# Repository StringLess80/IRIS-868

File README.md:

<div align="center">

# 📡 IRIS-868

**Custom embedded RF platform for the 868 MHz ISM band**

IRIS-868 is a custom embedded RF platform based on the STM32F303RET6 microcontroller and an Ebyte E22-900M22S (Semtech SX1262) sub-GHz LoRa module, designed for 868 MHz ISM-band wireless communication and data logging.

<br/>

<br/>

</div>

---

## ⚡ At a glance

|  |  |
|---|---|
| 🧠 **MCU** | STM32F303RET6 · Cortex-M4F @ 72 MHz · 512 KB flash · 64 + 16 KB RAM |
| 📻 **Radio** | Ebyte E22-900M22S · SX1262 · +22 dBm · LoRa / (G)FSK |
| 💾 **Storage** | Winbond W25Q128JV · 128 Mbit (16 MiB) SPI NOR flash for data logging |
| 🔌 **Power** | USB micro-B → AP2112K-3.3 LDO, filtered analog and RF rails, VBUS voltage monitoring on the ADC |
| 🧩 **Expansion** | 2 × 12-pin edge headers · I²C header for 128×64 OLED · 5-pin SWD with NRST · BOOT0 jumper · user button |
| 📐 **Board** | 2-layer FR4 · 78.8 × 36.6 mm · green mask, white silk · components on both sides |
| 🛠️ **Tooling** | KiCad 10, footprints and symbols embedded in the project files |

> [!WARNING]
> **Revision B is design-complete but has not been bring-up tested.** Fabrication files are released as-is. No firmware is included in this repository yet.

## 📑 Table of contents

- [What's new in revision B](#-whats-new-in-revision-b)
- [Gallery](#%EF%B8%8F-gallery)
- [System architecture](#%EF%B8%8F-system-architecture)
- [Repository layout](#-repository-layout)
- [Hardware overview](#-hardware-overview)
- [Pin assignment](#-pin-assignment)
- [Board specification](#-board-specification)
- [Bill of materials](#-bill-of-materials)
- [Getting started](#-getting-started)
- [Releases](#-releases)

## 🆕 What's new in revision B

| Area | Revision A | Revision B |
|---|---|---|
| **Expansion** | Most GPIOs unrouted | Two 1×12 edge headers (J5, J7) bring out power, reset, BOOT0, USART1 and 13 GPIOs |
| **Debug** | 4-pin SWD, no NRST | 5-pin SWD **with NRST** — "connect under reset" now works |
| **Storage** | — | 16 MiB W25Q128JV SPI flash on SPI3 (bottom side) |
| **User input** | Reset button only | Additional user button on **PC13** with RC debounce |
| **Monitoring** | — | VBUS divider (47 kΩ / 15 kΩ) on **PC0** for USB voltage measurement |
| **USB** | D+ pull-up fixed to +3.3 V | D+ pull-up driven by **PB8** — firmware-controlled attach/detach |
| **Radio** | E220-900M22S (LLCC68) | E22-900M22S (SX1262), same MCU connections |
| **Boot** | BOOT0 floats with no jumper | 100 kΩ pull-down (R13), boots from flash with no jumper |
| **Board** | 74.2 × 32.0 mm, single-sided assembly | 78.8 × 36.6 mm, bottom-side SMD parts and headers |

A design review before release added these changes:

- **RF feed:** the antenna trace no longer runs under the module, and J6 moved to suit (see [RF chain](#rf-chain)).
- **Decoupling:** C10 now sits next to the NRST pin, and C8 next to the VDDA pin.
- **Clean-up:** the unused test pad under IC1 was removed.
- **Fabrication:** design constraints follow JLCPCB's limits, with a green mask so the solder dams between LQFP pins can be kept.

## 🖼️ Gallery

<div align="center">

| Front | Back |
|:---:|:---:|
|  |  |

</div>

📄 Full schematic: [`docs/schematics/IRIS-868.pdf`](docs/schematics/IRIS-868.pdf)

## 🏗️ System architecture

```mermaid
flowchart LR
    USB["USB micro-B<br/>J2"] -->|VBUS 5 V| LDO["AP2112K-3.3<br/>600 mA LDO"]
    USB -.->|"D+ / D-"| ESD["USBLC6-2SC6<br/>ESD"]
    ESD -.-> MCU
    USB -->|"VBUS ÷ 4.13"| VMON["V_MON<br/>PC0 / ADC"]
    VMON --> MCU

    LDO --> RAIL(("3.3 V"))
    RAIL -->|"FB1 120 Ω"| VDDA["+3.3VA"]
    RAIL -->|"FB2 120 Ω"| VRF["VRF"]
    RAIL --> MCU
    VDDA --> MCU
    VRF --> MOD

    MCU["STM32F303RET6<br/>Cortex-M4F @ 72 MHz"]
    MCU <-->|"SPI1 · NSS · BUSY · DIO1 · NRST"| MOD["E22-900M22S<br/>SX1262 · +22 dBm"]
    MCU -->|"RXEN / TXEN"| MOD
    MOD -->|ANT| SMA["SMA edge<br/>J6"]

    MCU <-->|"SPI3 · CS"| FLASH["W25Q128JV<br/>16 MiB flash"]
    MCU <-->|"I²C1"| OLED["128×64 OLED<br/>header"]
    MCU <-->|"SWD + NRST"| DBG["ST-Link<br/>J3"]
    MCU <-->|"GPIO · USART1"| HDR["Edge headers<br/>J5 / J7"]
    BTN["User button<br/>PC13"] --> MCU
    MCU -.->|BOOT0| JMP["Boot jumper"]

    style MCU fill:#03234B,color:#fff
    style MOD fill:#2ea44f,color:#fff
    style FLASH fill:#8e44ad,color:#fff
    style RAIL fill:#f39c12,color:#fff
```

## 📁 Repository layout

```
IRIS-868/
├── CHANGELOG.md               Release history
├── hardware/
│   ├── kicad/                 KiCad 10 project (schematic, PCB, design rules)
│   │   └── libs/              Source symbols, footprints, 3D models
│   └── gerbers/
│       ├── rev.A/             Gerber and Excellon files, revision A
│       └── rev.B/             Gerber and Excellon files, revision B
├── production/BOM/            Interactive BOM for assembly
└── docs/
    ├── schematics/            Schematic PDF
    ├── images/                Board renders by revision
    └── datasheets/            Component reference documents
```

The schematic uses four top-level sheets, a KiCad 10 feature: MCU, crystal, reset, VBUS monitor and edge headers (`IRIS-868.kicad_sch`), power and USB (`pwr.kicad_sch`), the radio (`rf.kicad_sch`), and connectors, flash and the user button (`interfaces.kicad_sch`).

## 🔧 Hardware overview

### Power

USB VBUS feeds an **AP2112K-3.3** LDO (SOT-23-5, 600 mA) that generates the single 3.3 V system rail. Three domains branch from it:

| Rail | Source | Decoupling | Purpose |
|---|---|---|---|
| `+3.3V` | LDO output | 10 µF + 7 × 100 nF + 2 × 1 µF | MCU digital, I/O, flash, headers |
| `+3.3VA` | via FB1 (120 Ω ferrite) | 1 µF + 10 nF | STM32 VDDA / analog reference |
| `VRF` | via FB2 (120 Ω ferrite) | 22 µF + 1 µF + 2 × 100 nF | RF module supply |

The ferrite beads isolate the analog and RF domains from digital switching noise on the main rail, and C7 and C8 sit next to the VDDA pin. The 22 µF bulk capacitor on `VRF` supplies the current burst drawn by the module during transmission.

VBUS and +3.3 V are both available on header J5, so the board can supply a small carrier or add-on board.

### VBUS monitoring

A 47 kΩ / 15 kΩ divider (R6 / R7) scales VBUS onto `V_MON` (**PC0**, ADC12_IN6), filtered by C20 (100 nF). The divider ratio is 15 / 62, so 5.0 V on VBUS reads as about 1.21 V, and firmware recovers VBUS as `V_MON × 4.133`. The divider draws roughly 80 µA from VBUS, and its ~11 kΩ source impedance combined with C20 gives a stable input for the ADC sample-and-hold.

### RF chain

The E22-900M22S connects to the MCU over SPI1 plus four control lines. `RXEN` and `TXEN` drive the module's internal RF switch and must be managed by firmware around every transmit/receive transition. The antenna net (`ANT`) leaves the module's stamp-hole RF pad away from the module body and reaches the SMA edge connector as a 7.4 mm, 1.0 mm-wide coplanar trace on F.Cu, over an unbroken ground plane on B.Cu. A project design rule sets a 0.15 mm gap to the surrounding copper, which gives a calculated impedance of about 50 Ω with a 1.51 mm dielectric and εr 4.5. GND vias flank the feed.

### Data-logging flash

A **Winbond W25Q128JVSIQ** (SOIC-8, 208 mil) on the bottom side provides 16 MiB of non-volatile storage on **SPI3** (PC10 / PC11 / PC12) with chip select on **PD2**. The CS line has a 10 kΩ pull-up (R8) so the flash stays deselected while the MCU is in reset. `/WP` and `/HOLD` are tied high through R9 and R10, so the device operates in standard single-bit SPI mode; dual/quad I/O is not available on this revision. C21 decouples the flash locally.

### User input and reset

| Button | Net | Circuit |
|---|---|---|
| **SW1** (RST) | NRST (pin 7) | Pulls NRST low. 100 nF (C10) sits next to the pin on the bottom side. NRST is also on the SWD header and J5 |
| **SW2** (PC13) | PC13 (pin 2) | Active-low. 10 kΩ pull-up (R11), 10 kΩ series (R12), 100 nF (C22) to GND — about 1 ms fall / 2 ms rise debounce |

### USB

The USB D+ 1.5 kΩ pull-up (R2) is connected to **PB8** rather than to +3.3 V. Firmware must drive PB8 high to signal device attach to the host, and can drive it low to force a clean disconnect/re-enumeration without unplugging the cable.

### Interfaces

| Connector | Type | Pinout |
|---|---|---|
| **J2** USB | micro-B | USB FS device on PA11/PA12, D+ pull-up switched by PB8, ESD-protected |
| **J3** SWD | 1×5 @ 2.54 mm | `GND` · `NRST` · `SWCLK` · `SWDIO` · `+3.3V` |
| **J1** (BOOT0) | 1×3 @ 2.54 mm | `GND` · `BOOT0` · `+3.3V` — no jumper or 1–2 = flash, 2–3 = bootloader |
| **J4** (OLED) | 1×4 @ 2.54 mm | `GND` · `+3.3V` · `SCL` · `SDA` (1.5 kΩ pull-ups on board) |
| **J5** | 1×12 @ 2.54 mm, bottom-mounted | Power, reset, BOOT0, USART1, GPIO — see below |
| **J7** | 1×12 @ 2.54 mm, bottom-mounted | GPIO — see below |
| **J6** SMA | edge-mount | Antenna |

### Edge headers

J5 and J7 run along the long edges of the board with a row-to-row spacing of 31.75 mm (1.25 in). The header bodies are mounted on the bottom side, so the board can be plugged into a carrier with the components facing up. Pin 1 of each header is at the USB end.

| Pin | **J5** | **J7** |
|:---:|---|---|
| 1 | `GND` | `PB9` |
| 2 | `+3.3V` | `GND` |
| 3 | `VBUS` (5 V) | `PB0` |
| 4 | `NRST` | `PB1` |
| 5 | `BOOT0` | `PC4` |
| 6 | `PA9` (USART1_TX) | `PC5` |
| 7 | `PA10` (USART1_RX) | `PC6` |
| 8 | `GND` | `PC7` |
| 9 | `PB4` | `PC8` |
| 10 | `PB5` | `GND` |
| 11 | `PB6` | not connected |
| 12 | `PB8` ⚠️ USB D+ pull-up | not connected |

## 📌 Pin assignment

### STM32F303RET6 ↔ E22-900M22S

| STM32 pin | Signal | Module pin | Direction | Function |
|---|---|---|:---:|---|
| `PA5` | SPI1_SCK | 18 (SCK) | → | SPI clock |
| `PA6` | SPI1_MISO | 16 (MISO) | ← | SPI data out |
| `PA7` | SPI1_MOSI | 17 (MOSI) | → | SPI data in |
| `PA4` | NSS | 19 (NSS) | → | Chip select, active low |
| `PA3` | NRST | 15 (NRST) | → | Module reset, active low |
| `PA2` | BUSY | 14 (BUSY) | ← | Transceiver busy status |
| `PA8` | DIO1 | 13 (DIO1) | ← | Primary interrupt line |
| `PB10` | RXEN | 6 (RXEN) | → | RF switch, receive enable |
| `PB11` | TXEN | 7 (TXEN) | → | RF switch, transmit enable |

Module pin 8 (DIO2) is left unconnected in revision B.

### STM32F303RET6 ↔ W25Q128JV

| STM32 pin | Signal | Flash pin | Direction |
|---|---|---|:---:|
| `PC10` | SPI3_SCK | 6 (CLK) | → |
| `PC11` | SPI3_MISO | 2 (DO) | ← |
| `PC12` | SPI3_MOSI | 5 (DI) | → |
| `PD2` | FLASH_CS | 1 (/CS) | → |

<details>
<summary><b>Other pin assignments</b></summary>

<br/>

| STM32 pin | Function |
|---|---|
| `PA11` / `PA12` | USB D− / D+ |
| `PB8` | USB D+ pull-up control (also on J5 pin 12) |
| `PA13` / `PA14` | SWDIO / SWCLK |
| `PA15` | I²C1 SCL (AF4) |
| `PB7` | I²C1 SDA (AF4) |
| `PC0` | V_MON — VBUS voltage divider (ADC) |
| `PC13` | User button, active low |
| `PF0` / `PF1` | 16 MHz crystal (OSC_IN / OSC_OUT) |
| `NRST` (pin 7) | Reset button + 100 nF, SWD header, J5 |
| `BOOT0` (pin 60) | J1 via 10 kΩ (R1), 100 kΩ pull-down (R13), J5 (direct) |
| `PA9`, `PA10`, `PB4`–`PB6` | J5 |
| `PB0`, `PB1`, `PB9`, `PC4`–`PC8` | J7 |

The remaining GPIOs — `PA0`, `PA1`, `PB2`, `PB3`, `PB12`–`PB15`, `PC1`–`PC3`, `PC9`, `PC14`, `PC15` — are **not routed** in revision B.

</details>

## 📐 Board specification

| Parameter | Value |
|---|---|
| Dimensions | 78.8 × 36.6 mm, 2 mm corner radius |
| Layers | 2 (F.Cu / B.Cu), GND pour on both |
| Stackup | 1.6 mm FR4, 35 µm copper, εr 4.5 |
| Finish | HASL, green solder mask, white silkscreen |
| Vias | 327, 0.6 mm with 0.3 mm drill, tented |
| Minimum rules | Track 0.15 mm, clearance 0.2 mm, annular ring 0.13 mm, hole-to-hole 0.5 mm, copper-to-edge 0.2 mm |
| Assembly | Double-sided (U4, R8–R10, R13, C10, C21 and header bodies on the bottom) |
| Special rules | 0.15 mm clearance on the `ANT` coplanar feedline |

## 🧾 Bill of materials

<details>
<summary><b>Full BOM — 53 components</b></summary>

<br/>

| Ref | Qty | Value | Package | Notes |
|---|:---:|---|---|---|
| U1 | 1 | STM32F303RET6 | LQFP-64 | 0.5 mm pitch |
| U2 | 1 | AP2112K-3.3 | SOT-23-5 | 600 mA LDO |
| U3 | 1 | USBLC6-2SC6 | SOT-23-6 | USB ESD protection |
| U4 | 1 | W25Q128JVSIQ | SOIC-8 5.3 × 5.3 mm | 128 Mbit SPI flash, **bottom side** |
| IC1 | 1 | E22-900M22S | Ebyte SMD module | SX1262, +22 dBm |
| Y1 | 1 | 16 MHz | 3225-4pin | CL ≈ 10 pF, ≤20 ppm recommended |
| C1–C5, C10, C16, C17, C19, C21 | 10 | 100 nF | 0402 | 16 V X7R — C10 and C21 on bottom side |
| C20, C22 | 2 | 100 nF | 0805 | 16 V X7R — V_MON filter, PC13 debounce |
| C8, C9, C14, C15 | 4 | 1 µF | 0402 | 16 V X5R/X7R |
| C13 | 1 | 1 µF | 0402 | **25 V** — sits on the 5 V VBUS rail |
| C6 | 1 | 10 µF | 0603 | 16 V X5R |
| C18 | 1 | 22 µF | 0805 | 16 V X5R, RF bulk |
| C7 | 1 | 10 nF | 0402 | 16 V X7R, VDDA filter |
| C11, C12 | 2 | 12 pF | 0402 | **50 V C0G/NP0 ±5%**, crystal load |
| R1 | 1 | 10 kΩ | 0402 | BOOT0 series |
| R2 | 1 | 1.5 kΩ | 0402 | USB D+ pull-up (to PB8) |
| R3 | 1 | 1.5 kΩ | 0402 | Power LED series |
| R4, R5 | 2 | 1.5 kΩ | 0402 | I²C pull-ups |
| R6 | 1 | 47 kΩ | 0402 | VBUS divider, top — 1% recommended |
| R7 | 1 | 15 kΩ | 0402 | VBUS divider, bottom — 1% recommended |
| R8, R9, R10 | 3 | 10 kΩ | 0402 | Flash /CS, /WP, /HOLD pull-ups, **bottom side** |
| R11, R12 | 2 | 10 kΩ | 0402 | PC13 button pull-up / series |
| R13 | 1 | 100 kΩ | 0402 | BOOT0 pull-down, **bottom side** |
| FB1, FB2 | 2 | 120 Ω @ 100 MHz | 0402 | Analog / RF rail filtering, rated ≥ 500 mA |
| D1 | 1 | Red LED | 0603 | Power indicator |
| SW1, SW2 | 2 | Tactile switch | 6 mm THT | 4-pin, 4.5 × 6.5 mm, marked RST and PC13 |
| J1 | 1 | Pin header 1×3 | 2.54 mm | BOOT0 select, marked BOOT0 |
| J2 | 1 | USB micro-B | Würth 629105150521 | |
| J3 | 1 | Pin header 1×5 | 2.54 mm | SWD + NRST |
| J4 | 1 | Pin header 1×4 | 2.54 mm | I²C / OLED, marked OLED |
| J5, J7 | 2 | Pin header 1×12 | 2.54 mm | Edge headers, **bottom side** |
| J6 | 1 | SMA edge-mount | RF Solutions CON-SMA-EDGE-S | |

</details>

For assembly, open the [interactive BOM](production/BOM/IRIS-868_iBOM_revB.html) after downloading it.

> [!TIP]
> Capacitor voltage ratings account for MLCC **DC bias derating** — class II ceramics lose a large fraction of their nominal capacitance near their rated voltage, so ratings are specified at roughly 4–5× the working voltage. A **2.54 mm jumper shunt** on J1 is needed only to enter the bootloader, and it isn't part of the PCB BOM.

## 🚀 Getting started

<details open>
<summary><b>1 · Fabricate the board</b></summary>

<br/>

Fabrication files for revision B are in [`hardware/gerbers/rev.B/`](hardware/gerbers/rev.B/), as Gerber and Excellon drill files. A ready-to-upload zip is attached to the [`v2.0.0` release](https://github.com/StringLess80/IRIS-868/releases/tag/v2.0.0).

- Process: standard 2-layer, 1.6 mm FR4, 1 oz copper, HASL or ENIG, green mask
- No controlled impedance is specified
- Revision B has SMD parts on **both sides**. If using assembly service, request double-sided assembly or have the bottom-side parts (U4, R8–R10, R13, C10, C21) left unpopulated and fit them by hand
- Suggested hand-assembly order: bottom-side SMD parts first, then the STM32 (drag solder, then inspect with flux and a loupe), then the remaining ICs, then passives, then the module, then through-hole parts last — edge headers J5/J7 go in from the bottom

</details>

<details>
<summary><b>2 · Open the design</b></summary>

<br/>

The project requires **KiCad 10** or later, because it uses multiple top-level sheets. Symbols and footprints are embedded in the project files, so it opens without any library setup. Sources for the non-standard parts (E22 module, SMA edge connector) and the 3D models are under `hardware/kicad/libs/`. DRC reports one library warning on J6, because its source library is not registered in the project.

```bash
git clone https://github.com/StringLess80/IRIS-868.git
cd IRIS-868
kicad hardware/kicad/IRIS-868.kicad_pro
```

</details>

<details>
<summary><b>3 · Program it</b></summary>

<br/>

**Via SWD (recommended)** — connect an ST-Link or any CMSIS-DAP probe to J3, including the NRST line. Because NRST is on the header, "connect under reset" works, so a board with firmware that disables SWD or enters low-power mode early can still be recovered from the debugger.

```bash
st-flash --reset write firmware.bin 0x08000000
```

**Via UART bootloader** — connect a 3.3 V USB-serial adapter to J5 (`PA9` = MCU TX, `PA10` = MCU RX, `GND`), fit the J1 jumper on pins 2–3 and reset:

```bash
stm32flash -w firmware.bin -v -g 0x0 /dev/ttyUSB0
```

**Via USB DFU** — the ROM bootloader does not drive PB8, so the D+ pull-up is inactive and the host will not see the device. Tie J5 pin 12 (`PB8`) to J5 pin 2 (`+3.3V`) for the duration of the DFU session, fit the J1 jumper on pins 2–3, reset, then:

```bash
dfu-util -a 0 -s 0x08000000:leave -D firmware.bin
```

> [!CAUTION]
> Remove the PB8 link before running application firmware — if firmware drives PB8 low while it is tied to +3.3 V, the pin is shorted.

Remove the jumper, or move it to pins 1–2, and reset to run from flash.

</details>

## 📦 Releases

| Version | Hardware | Status |
|---|---|---|
| [`v2.0.0`](https://github.com/StringLess80/IRIS-868/releases/tag/v2.0.0) | Revision B | Released for fabrication, not bring-up tested |
| [`v1.0.0`](https://github.com/StringLess80/IRIS-868/releases/tag/v1.0.0) | Revision A | Superseded |

The major version changes with each PCB revision. Minor and patch versions cover compatible changes to the BOM, documentation or fabrication outputs. See the [changelog](CHANGELOG.md) for details.

<div align="center">
<br/>

Made with [KiCad](https://www.kicad.org/) 🛠️

</div>

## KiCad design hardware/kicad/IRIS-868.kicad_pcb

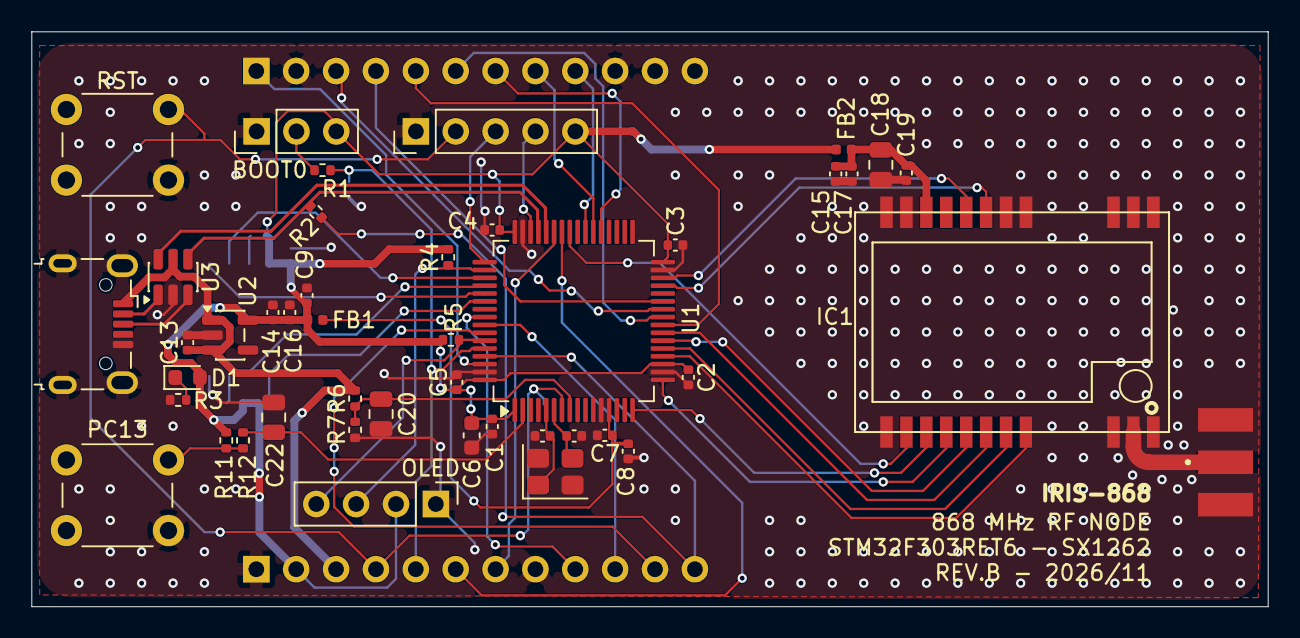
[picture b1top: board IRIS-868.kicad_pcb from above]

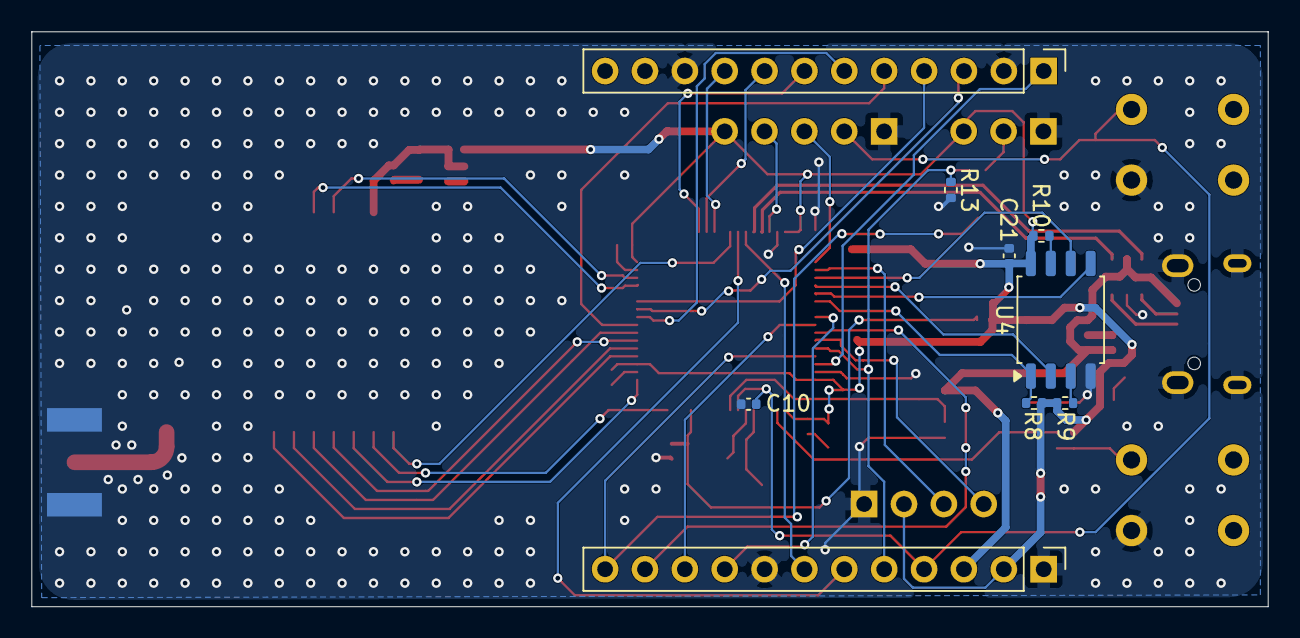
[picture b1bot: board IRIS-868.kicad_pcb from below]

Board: 2 copper layers, 78.8 x 36.6 mm, 53 parts (9 on the bottom side), 52 nets.

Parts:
C1, C2, C3, C4, C5, C10, C16, C17, C19, C21: 100 nF; C_0402_1005Metric
C6: 10 uF; C_0603_1608Metric
C7: 10 nF; C_0402_1005Metric
C8, C9, C13, C14, C15: 1 uF; C_0402_1005Metric
C11, C12: 12 pF; C_0402_1005Metric
C18: 22 uF; C_0805_2012Metric
C20, C22: 100 nF; C_0805_2012Metric
D1: RED; LED_0603_1608Metric
FB1, FB2: 120 R; L_0402_1005Metric
IC1: E22-900M22S
J1: PRG; PinHeader_1x03_P2.54mm_Vertical
J2: USB_B_Micro; USB_Micro-B_Wuerth_629105150521
J3: SWD; PinHeader_1x05_P2.54mm_Vertical
J4: 128x64 OLED; PinHeader_1x04_P2.54mm_Vertical
J5, J7: Conn_01x12_Pin; PinHeader_1x12_P2.54mm_Vertical
J6: SMA; RFSOLUTIONS_CON-SMA-EDGE-S
R1: 10 k; R_0402_1005Metric
R2, R3, R4, R5: 1k5; R_0402_1005Metric
R6: 47k; R_0402_1005Metric
R7: 15k; R_0402_1005Metric
R8, R9, R10, R11, R12: 10k; R_0402_1005Metric
R13: 100k; R_0402_1005Metric
SW1: RST; SW_PUSH_6mm
SW2: BTN; SW_PUSH_6mm
U1: STM32F303RET6; LQFP-64_10x10mm_P0.5mm
U2: AP2112K-3.3; SOT-23-5
U3: USBLC6-2SC6; SOT-23-6
U4: W25Q128JVSIQ; SOIC-8_5.3x5.3mm_P1.27mm
Y1: 16 MHz; Crystal_SMD_3225-4Pin_3.2x2.5mm

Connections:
+3.3V: C1.1, C2.1, C3.1, C4.1, C5.1, C6.1, C9.1, C14.1, C16.1, C21.1, D1.2 (A), FB1.2, FB2.1, J1.3, J3.5, J4.2, J5.2, R4.2, R5.2, R8.1, R9.1, R10.1, R11.2, U1.1 (VBAT), U1.19 (VDD), U1.32 (VDD), U1.48 (VDD), U1.64 (VDD), U2.5 (VOUT), U4.8 (VCC)
+3.3VA: C7.1, C8.1, FB1.1, U1.13 (VDDA)
/PWR-USB/PWR_LED_K: D1.1 (K), R3.2
/Root/J_BOOT0: J1.2, R1.1
ANT: IC1.21 (ANT), J6.1
BOOT0: J5.5, R1.2, R13.1, U1.60 (BOOT0)
BTN: C22.1, R12.1, U1.2 (PC13)
BUSY: IC1.14 (BUSY), U1.16 (PA2)
DIO1: IC1.13 (DIO1), U1.41 (PA8)
FLASH_~CS: R8.2, U1.54 (PD2), U4.1 (~CS)
GND: C1.2, C2.2, C3.2, C4.2, C5.2, C6.2, C7.2, C8.2, C9.2, C10.2, C11.2, C12.2, C13.2, C14.2, C15.2, C16.2, C17.2, C18.2, C19.2, C20.2, C21.2, C22.2, IC1.1 (GND), IC1.2 (GND), IC1.3 (GND), IC1.4 (GND), IC1.5 (GND), IC1.10 (GND), IC1.11 (GND), IC1.12 (GND), IC1.20 (GND), IC1.22 (GND), J1.1, J2.5 (GND), J2.SH (Shield), J3.1, J4.1, J5.1, J5.8, J6.G1, J6.G2, J6.G3, J6.G4, J7.2, J7.10, R3.1, R7.1, R13.2, SW1.2, SW2.2, U1.12 (VSSA), U1.18 (VSS), U1.31 (VSS), U1.47 (VSS), U1.63 (VSS), U2.2 (GND), U3.2 (GND), U4.4 (GND), Y1.2 (G), Y1.4 (G)
I2C1_SCL: J4.3, R4.1, U1.50 (PA15)
I2C1_SDA: J4.4, R5.1, U1.59 (PB7)
unnamed: J2.3 (D+), U3.3 (I/O2)
unnamed: J2.2 (D-), U3.1 (I/O1)
unnamed: R11.1, R12.2, SW2.1
unnamed: R10.2, U4.7 (~HOLD/~RESET/IO_{3})
unnamed: R9.2, U4.3 (~WP/IO_{2})
OSC_IN: C11.1, U1.5 (PF0), Y1.1
OSC_OUT: C12.1, U1.6 (PF1), Y1.3
PA9: J5.6, U1.42 (PA9)
PA10: J5.7, U1.43 (PA10)
PB0: J7.3, U1.26 (PB0)
PB1: J7.4, U1.27 (PB1)
PB4: J5.9, U1.56 (PB4)
PB5: J5.10, U1.57 (PB5)
PB6: J5.11, U1.58 (PB6)
PB8: J5.12, R2.2, U1.61 (PB8)
PB9: J7.1, U1.62 (PB9)
PC4: J7.5, U1.24 (PC4)
PC5: J7.6, U1.25 (PC5)
PC6: J7.7, U1.37 (PC6)
PC7: J7.8, U1.38 (PC7)
PC8: J7.9, U1.39 (PC8)
RXEN: IC1.6 (RXEN), U1.29 (PB10)
SP1_MISO: IC1.16 (MISO), U1.22 (PA6)
SP1_MOSI: IC1.17 (MOSI), U1.23 (PA7)
SPI1_SCK: IC1.18 (SCK), U1.21 (PA5)
SPI3_MISO: U1.52 (PC11), U4.2 (DO/IO_{1})
SPI3_MOSI: U1.53 (PC12), U4.5 (DI/IO_{0})
SPI3_SCK: U1.51 (PC10), U4.6 (CLK)
SWCLK: J3.3, U1.49 (PA14)
SWDIO: J3.4, U1.46 (PA13)
TXEN: IC1.7 (TXEN), U1.30 (PB11)
USB_D+: R2.1, U1.45 (PA12), U3.4 (I/O2)
USB_D-: U1.44 (PA11), U3.6 (I/O1)
VBUS: C13.1, J2.1 (VBUS), J5.3, R6.2, U2.1 (VIN), U2.3 (EN), U3.5 (VBUS)
VRF: C15.1, C17.1, C18.1, C19.1, FB2.2, IC1.9 (VCC)
V_{MON}: C20.1, R6.1, R7.2, U1.8 (PC0)
~NRST: IC1.15 (NRST), U1.17 (PA3)
~RST: C10.1, J3.2, J5.4, SW1.1, U1.7 (NRST)
~SS: IC1.19 (NSS), U1.20 (PA4)
